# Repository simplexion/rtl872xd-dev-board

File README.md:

# RTL872xD Development Board
Development board(s) for the Realtek [RTL872xD](https://www.realtek.com/en/products/communications-network-ics/item/rtl8721dm) dual band WLAN and BLE MCU.
Please view the [product page](https://www.realmcu.com/en/Home/Product/a6248c82-7c9a-4f79-bebf-0df240726c4d) for detailed information and documentation.

Browse the files on [KiCanvas](https://kicanvas.org/?github=https://github.com/simplexion/rtl872xd-dev-board/tree/main/source/rtl872xd-dev-board) - by [Stargirl Flowers](https://github.com/theacodes)

## Directory Structure
| directory  | content                                                              |
|------------|----------------------------------------------------------------------|
| source     | KiCad project directories                                            |
| production | fabrication files (Gerber, BOM, placement)                           |
| exports    | schematic and layout plots, board 3D model and renderings            |
| datasheets | component datasheets                                                 |
| assets     | board setups, component 3D models, logos                             |
| scripts    | BOM export plugins, miscellaneous helper scripts for file conversion |
| hooks      | git hooks, for example for automatic documentation export            |

## Automation
This repository contains a Makefile that automates PDF and Gerber export.

### Requirements
Apart from [KiCad 7](#kicad-version) this requires some additional software.

The Makefile calls a Python script that makes use of [sexptdata](https://pypi.org/project/sexpdata/) to parse KiCad files.
Install [Poetry](https://python-poetry.org/) and run `poetry shell` followed by `poetry install` in the root of this repositoryto set up a virtual environment with the required package(s). To re-enter this environment, simply run `poetry shell` in the root of this repository.

For PDF export you additonally need to install [Poppler](https://poppler.freedesktop.org/).
Gerber export requires [zip](https://infozip.sourceforge.net/).

#### Nix(OS)
If you are using the Nix package manager, you can enter a development environment
with KiCad and all other software by running `nix-shell` in the root of this
repository.

### Export
To export all PDFs and production files, simply run
```shell
make
```
PDFs and production files are exported automatically when you `git commit`, if you have
[Git Hooks](#installing-git-hooks-optional) set up.

### Installing Git Hooks (optional)
The [hooks](hooks) directory contains client-side [git hooks](https://git-scm.com/book/en/v2/Customizing-Git-Git-Hooks).
Currently only the pre-commit hook is used to automatically export plots.

To enable the hooks locally, run the following in the root of the repository.
```shell
git config core.hooksPath ./hooks
```

## KiCad Version
Version information of the KiCad used to generate the files.
```
[nix-shell:~/repos/kicad-template]$ kicad-cli version --format about

Application: kicad-cli x86_64 on x86_64

Version: 7.0.1, release build

Libraries:
        wxWidgets 3.2.2
        FreeType 2.12.1
        HarfBuzz 6.0.0
        FontConfig 2.14.0
        libcurl/7.87.0 OpenSSL/3.0.8 zlib/1.2.13 brotli/1.0.9 zstd/1.5.2 libidn2/2.3.2 libssh2/1.10.0 nghttp2/1.51.0

Platform: , 64 bit, Little endian, wxBase, , wayland

Build Info:
        Date: Jan  1 1980 00:00:00
        wxWidgets: 3.2.2 (wchar_t,wx containers) GTK+ 0.0
        Boost: 1.79.0
        OCC: 7.6.2
        Curl: 7.87.0
        ngspice: 37
        Compiler: GCC 12.2.0 with C++ ABI 1017

Build settings:
        KICAD_USE_EGL=ON
        KICAD_SPICE=ON
```

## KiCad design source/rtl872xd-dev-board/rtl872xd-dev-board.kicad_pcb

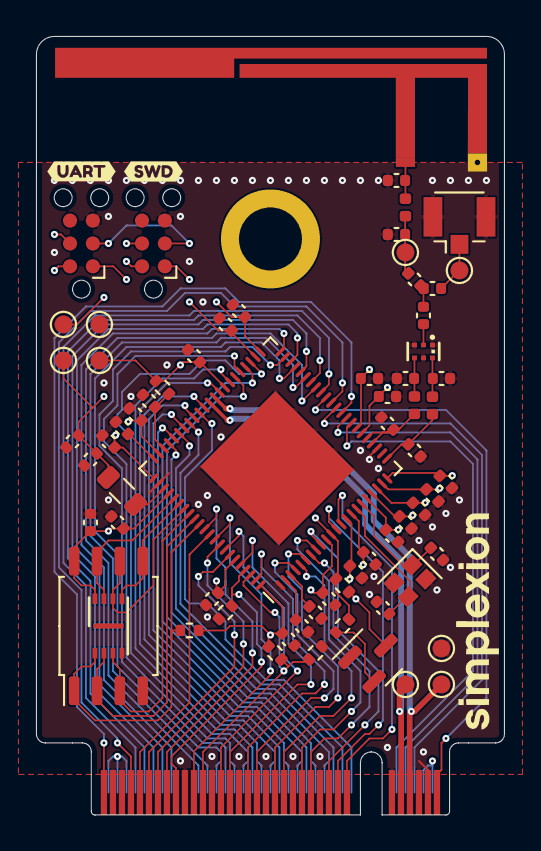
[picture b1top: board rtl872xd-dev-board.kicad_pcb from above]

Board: 4 copper layers, 26.0 x 43.2 mm, 69 parts (0 on the bottom side), 76 nets.

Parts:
AE1: Antenna_Shield; AKK_2.4GHz_5GHz_Left
C1: 0.4p; C_0402_1005Metric
C2: 0.3p; C_0402_1005Metric
C3: 0.5p; C_0402_1005Metric
C4: 1.0p; C_0402_1005Metric
C5, C6: 0R; C_0402_1005Metric
C7, C8, C11, C12: C; C_0402_1005Metric
C9: 1.8p; C_0402_1005Metric
C10, C17, C19, C20, C21, C22, C23, C24, C25, C26, C27, C28, C30, C32: 100n; C_0402_1005Metric
C13, C36: 1u; C_0402_1005Metric
C14: 4.7n; C_0402_1005Metric
C15, C29, C34, C35: 2.2u; C_0402_1005Metric
C16: 10u; C_0402_1005Metric
C18: 1n; C_0402_1005Metric
C31: 4.7u; C_0402_1005Metric
C33: C_0402_1005Metric
DP1: MDPX18M1524P69-D03; DP_0603_1608Metric
J1: Conn_Coaxial; U.FL_Hirose_U.FL-R-SMT-1_Vertical
J2: Bus_M.2_Socket_B; M.2-B-KEY-22x
J3, J4: Conn_ARM_SWD_TagConnect_TC2030-NL; Tag-Connect_TC2030-IDC-NL_2x03_P1.27mm_Vertical
L1: 1n; L_0402_1005Metric
L2: 3.3n; L_0402_1005Metric
L3: L; L_0402_1005Metric
L4: 2.2u; L_0805_2012Metric
R1, R2, R3, R4: 10k; R_0402_1005Metric
R5: 12k; R_0402_1005Metric
R6: 200; R_0402_1005Metric
R7: 1k; R_0402_1005Metric
TP1, TP2, TP3, TP4, TP5, TP6, TP7, TP8, TP9: TestPoint; TestPoint_Pad_D1.0mm
U1: RTL8722DM; QFN-88_EP_10x10_Pitch0.4mm
U2: W25Q128JVS; SOIC-8_5.23x5.23mm_P1.27mm
U3: W25Q16JV; USON-8_3.0x2.0mm_P0.5mm
U4: LM809; SOT-23
Y1: 40MHz; Crystal_SMD_2016-4Pin_2.0x1.6mm
kibuzzard-6492E3AE: G***; kibuzzard-6492E3AE
kibuzzard-6492E3B2: G***; kibuzzard-6492E3B2

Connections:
+3.3V: C10.1, C17.2, C18.2, C20.2, C23.2, C24.2, C25.2, C27.2, C28.2, C32.2, C34.2, C36.2, J2.2 (3.3V), J2.4 (3.3V), J2.70 (3.3V), J2.72 (3.3V), J2.74 (3.3V), J3.1 (VCC), J4.1 (VCC), R1.2, R2.1, R3.2, R6.1, TP7.1, U1.10 (VD1833_GPIO), U1.15 (VA1833_XTAL), U1.18 (VR1833_SYN), U1.21 (VR1833_PAD_A), U1.22 (VR1833_PA_A), U1.28 (VR1833_PA_G), U1.45 (VD1833_GPIO), U1.52 (VA1833_USB), U1.67 (VD1833_PMU), U1.70 (VD1833_SPS/VD1833_FLASH), U1.88 (AVCC_DRIV), U2.8 (VCC), U3.8 (VCC), U4.3 (VCC)
/Flash/QSPI.CLK: U1.73 (SPI_CLK), U2.6 (CLK), U3.6 (CLK)
/Flash/QSPI.IO0: U1.72 (SPI_IO0), U2.5 (DI(IO0)), U3.5 (DI(IO0))
/Flash/QSPI.IO1: U1.75 (SPI_IO1), U2.2 (DO(IO1)), U3.2 (DO(IO1))
/Flash/QSPI.IO2: U1.74 (SPI_IO2), U2.3 (IO2), U3.3 (IO2)
/Flash/QSPI.IO3: U1.71 (SPI_IO3), U2.7 (IO3), U3.7 (IO3)
/Flash/QSPI.~CS: R1.1, U1.76 (SPI_~CS), U2.1 (~CS), U3.1 (~CS)
/PA0: J2.41 (PERn0/SATA-B+), U1.4 (PA0/MIC_BIAS)
/PA1: J2.29 (PERn1/USB3.0-Rx-/SSIC-RxN), U1.7 (PA1/MIC2_N)
/PA2: J2.37 (PETp1/USB3.0-Tx+/SSIC-TxP), U1.6 (PA2/MIC2_P)
/PA4: J2.35 (PETn1/USB3.0-Tx-/SSIC-TxN), U1.5 (PA4/MIC1_P)
/PA5: J2.31 (PERp1/USB3.0-Rx+/SSIC-RxP), U1.8 (PA5/AUXIN_L)
/PA6: J2.25 (DPR), U1.9 (PA6/AUXIN_R)
/PA9: J2.10 (GPIO_9/DAS/~DSS/~LED1), U1.30 (PA9)
/PA10: J2.8 (~W_DISABLE1), U1.31 (PA10)
/PA11: J2.75 (CONFIG_2), U1.32 (PA11)
/PA12: J2.6 (~FULL_CARD_POWER_OFF), U1.33 (PA12)
/PA13: J2.69 (CONFIG_1), U1.34 (PA13)
/PA14: J2.1 (CONFIG_3), U1.35 (PA14)
/PA15: J2.68 (SUSCLK), U1.36 (PA15)
/PA16: J2.54 (~PEWAKE), U1.37 (PA16)
/PA17: J2.66 (SIM_DETECT), U1.38 (PA17)
/PA18: J2.52 (~CLKREQ), U1.39 (PA18)
/PA19: J2.64 (COEX1), U1.40 (PA19)
/PA20: J2.50 (~PERST), U1.41 (PA20)
/PA21: J2.62 (COEX2), U1.42 (PA21)
/PA22: J2.48 (GPIO_4), U1.43 (PA22)
/PA23: J2.60 (COEX3), U1.44 (PA23)
/PA24: J2.44 (GPIO_2), U1.47 (PA24)
/PA28: J2.40 (GPIO_0), U1.53 (PA28/RREF)
/PA30: J2.42 (GPIO_1), U1.51 (PA30/SPS_SEL)
/PA31: J2.46 (GPIO_3), U1.49 (PA31)
/PB0: J2.28 (GPIO_8), U1.50 (PB0)
/PB1: J2.20 (GPIO_5), U1.57 (PB1/ADC_CH4)
/PB2: J2.38 (DEVSLP), U1.56 (PB2/ADC_CH5)
/PB4: J2.22 (GPIO_6), U1.59 (PB4/TOUCH_KEY0)
/PB5: J2.34 (UIM-DATA), U1.60 (PB5/TOUCH_KEY1)
/PB6: J2.24 (GPIO_7), U1.61 (PB6/TOUCH_KEY2)
/PB7: J2.32 (UIM-CLK), U1.62 (PB7/TOUCH_KEY3)
/PB18: J2.61 (ANTCTL1), U1.77 (PB18)
/PB19: J2.67 (~RESET), U1.78 (PB19)
/PB20: J2.55 (REFCLKp), U1.79 (PB20)
/PB21: J2.63 (ANTCTL2), U1.80 (PB21)
/PB22: J2.49 (PETp0/SATA-A+), U1.81 (PB22)
/PB23: J2.65 (ANTCTL3), U1.82 (PB23)
/PB28: J2.59 (ANTCTL0), R5.2, U1.85 (PB28/AOUTN_R)
/PB29: J2.47 (PETn0/SATA-A-), U1.84 (PB29/AOUTP_R)
/PB30: J2.53 (REFCLKn), R3.1, R4.2, U1.86 (PB30/AOUTN_L)
/PB31: J2.43 (PERp0/SATA-B-), U1.87 (PB31/AOUTP_L)
/Power & Clock/VA1833_PLL: C29.2, R6.2, U1.64 (VA1833_PLL)
/RF/RFIO_A: C2.1, L1.1, U1.23 (RFIO_A)
/RF/RFIO_G: C4.1, L2.1, U1.26 (RFIN_G), U1.27 (RFOUT_G)
/SWD.SWCLK: J2.36 (UIM-PWR), J3.4 (SWCLK), U1.58 (PB3/ADC_CH6/SWD_CLK)
/SWD.SWDIO: J2.30 (UIM-RESET), J3.2 (SWDIO), U1.48 (PA27/SWD_DATA)
/UART_{LOG}.RX: J2.21 (CONFIG_0), J4.4 (SWCLK), U1.13 (PA8/UART_LOG_RXD)
/UART_{LOG}.TX: J2.23 (GPIO_11), J4.2 (SWDIO), U1.12 (PA7/UART_LOG_TXD)
/VBAT_MEAS: J2.26 (GPIO_10), U1.63 (VBAT_MEAS)
/~RESET: J3.3 (~RESET), J4.3 (~RESET), R2.2, R7.2, TP5.1, U1.11 (CHIP_EN)
D+: J2.7 (USB_D+), TP3.1, U1.54 (PA26/HSDP)
D-: J2.9 (USB_D-), TP4.1, U1.55 (PA25/HSDM)
GND: AE1.2 (Shield), C1.2, C2.2, C3.2, C4.2, C7.2, C8.2, C10.2, C11.2, C12.2, C13.1, C14.1, C15.2, C16.1, C17.1, C18.1, C19.2, C20.1, C21.2, C22.2, C23.1, C24.1, C25.1, C26.2, C27.1, C28.1, C29.1, C30.2, C31.1, C32.1, C33.1, C34.1, C35.2, C36.1, DP1.1, DP1.3 (GND), DP1.5 (GND), J1.2 (Ext), J2.3 (GND), J2.5 (GND), J2.11 (GND), J2.27 (GND), J2.33 (GND), J2.39 (GND), J2.45 (GND), J2.51 (GND), J2.57 (GND), J2.71 (GND), J2.73 (GND), J3.5 (GND), J4.5 (GND), R4.1, R5.1, TP8.1, TP9.1, U1.1 (AUDIO_GND), U1.25 (RFGND), U1.68 (GNDSPS), U1.89 (GND), U2.4 (GND), U3.4 (GND), U4.1 (GND), Y1.2, Y1.4
unnamed: AE1.1 (A), C8.1, L3.2
unnamed: C5.2, C6.1, C9.1
unnamed: C6.2, C7.1, L3.1, TP2.1
unnamed: C5.1, DP1.2 (C)
unnamed: C1.1, DP1.6 (H), L1.2
unnamed: C3.1, DP1.4 (L), L2.2
unnamed: C9.2, J1.1 (In), TP1.1
unnamed: C14.2, U1.3 (AUDIO_VREF)
unnamed: C13.2, U1.2 (AVCC)
unnamed: L4.1, U1.69 (SW_LX)
unnamed: C31.2, U1.66 (VD18_PSRAM)
unnamed: C11.1, U1.17 (XI), Y1.1
unnamed: C12.1, U1.16 (XO), Y1.3
unnamed: R7.1, U4.2 (~RESET)
VDD: C15.1, C16.2, C19.1, C21.1, C22.1, C26.1, C30.1, C33.2, C35.1, L4.2, TP6.1, U1.14 (VA11_AFE), U1.19 (VR11_SYN), U1.20 (VR11_RF2), U1.29 (VR11_RF1), U1.46 (VD11_CORE), U1.65 (VA11_PLL), U1.83 (VD11_CORE)

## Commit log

2023-04-28 added library submodule
2023-04-28 Initial commit for rtl872xd-dev-board
2023-06-20 finished prelim layout
2023-06-20 added renderingsg
2023-06-21 added TC2030 debug ports
2023-06-21 remove unused schematic
2023-06-21 resolve all ERC error, reduce number of warnings
2023-06-21 tidied up like Marie Kondo
2023-06-29 first production version
